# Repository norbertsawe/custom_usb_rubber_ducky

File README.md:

# Nodus — RP2040 Custom USB Keystroke Injection Platform

**Nodus** is a custom, ultra-compact USB Human Interface Device (HID) platform designed for keystroke injection, automated penetration testing, and security research. Powered by the Raspberry Pi RP2040 microcontroller, the board features dedicated high-speed QSPI flash memory, a precision external crystal oscillator for reliable USB PHY timing, and hardware physical controls for rapid reset and bootloader recovery.

---

## 📷 Board Hardware Overview

The PCB is custom designed in a standard USB stick form factor with an integrated PCB USB-A plug:

### Key Hardware Features

* **Microcontroller:** Raspberry Pi RP2040 Dual-Core ARM Cortex-M0+ running up to 133 MHz.
* **Storage:** High-speed QSPI NOR Flash IC for payload scripts and custom firmware storage.
* **Clock Source:** External 12 MHz Crystal Oscillator ensuring strict USB 2.0 full-speed timing stability.
* **On-Board Controls:**
  * **`B` (BOOTSEL):** Physical tactile button to force UF2 bootloader mode upon startup.
  * **`R` (RESET):** Hardware reset button for fast rebooting and rapid payload re-execution cycles without unplugging the drive.
* **Form Factor:** Slim, low-profile SMT design tailored for standard custom USB flash drive enclosures.

---

## 📊 Technical Specifications

| Component | Specification / Notes |
| :--- | :--- |
| **Core Processor** | RP2040 (Dual ARM Cortex-M0+, 264KB SRAM) |
| **Clock Source** | 12.000 MHz SMD Crystal Oscillator ($\pm$20 ppm) |
| **Flash Memory** | External QSPI NOR Flash (W25Qxx series or equivalent) |
| **Interface** | USB 2.0 Full-Speed (12 Mbps) Male USB-A Connector |
| **Power Supply** | 5V VBUS regulated via low-dropout (LDO) regulator to 3.3V |
| **Status Indicators** | Configurable User/Status LED(s) |
| **Debug & Control** | Tactical Boot/Reset switches, SWD target pads |

---

## 📁 Repository Structure

```

.
├── Hardware/            # KiCad schematics (.kicad_sch), PCB layouts (.kicad_pcb), and Gerber outputs
├── README.md            # Project overview and instructions
├── rubber_ducky_img1.png
├── rubber_ducky_img2.png
├── rubber_ducky_img3.png
└── rubber_ducky_img4.png

```

---

## 🚀 Quickstart & Hardware Testing

### 1. Putting the Board into Bootloader Mode
1. Plug the Nodus device into a host computer USB port.
2. Hold down the **`B` (BOOTSEL)** button and press the **`R` (RESET)** button once (or plug the device in while holding **`B`**).
3. Release the **`B`** button.
4. The device will enumerate as an external mass storage drive named `RPI-RP2`.

---

## 🛠 Firmware Development (WIP)

> [!NOTE]
> **Work In Progress:** Custom payload engines and dedicated firmware drivers are currently under active development. Hardware architecture and memory configurations are finalized.

Target build process once the C/C++ SDK engine is integrated:

```bash
cd Firmware
mkdir build && cd build
cmake ..
make -j$(nproc)

```

---

> [!WARNING]
> **Security & Usage Disclaimer**
> This hardware platform is intended exclusively for authorized security auditing, educational purposes, penetration testing, and legitimate research activities. Always obtain explicit written permission from system owners before testing or running payloads on any host environment.

---

## 📜 License

This project is licensed under the MIT License. See the `LICENSE` file for details.

```

```

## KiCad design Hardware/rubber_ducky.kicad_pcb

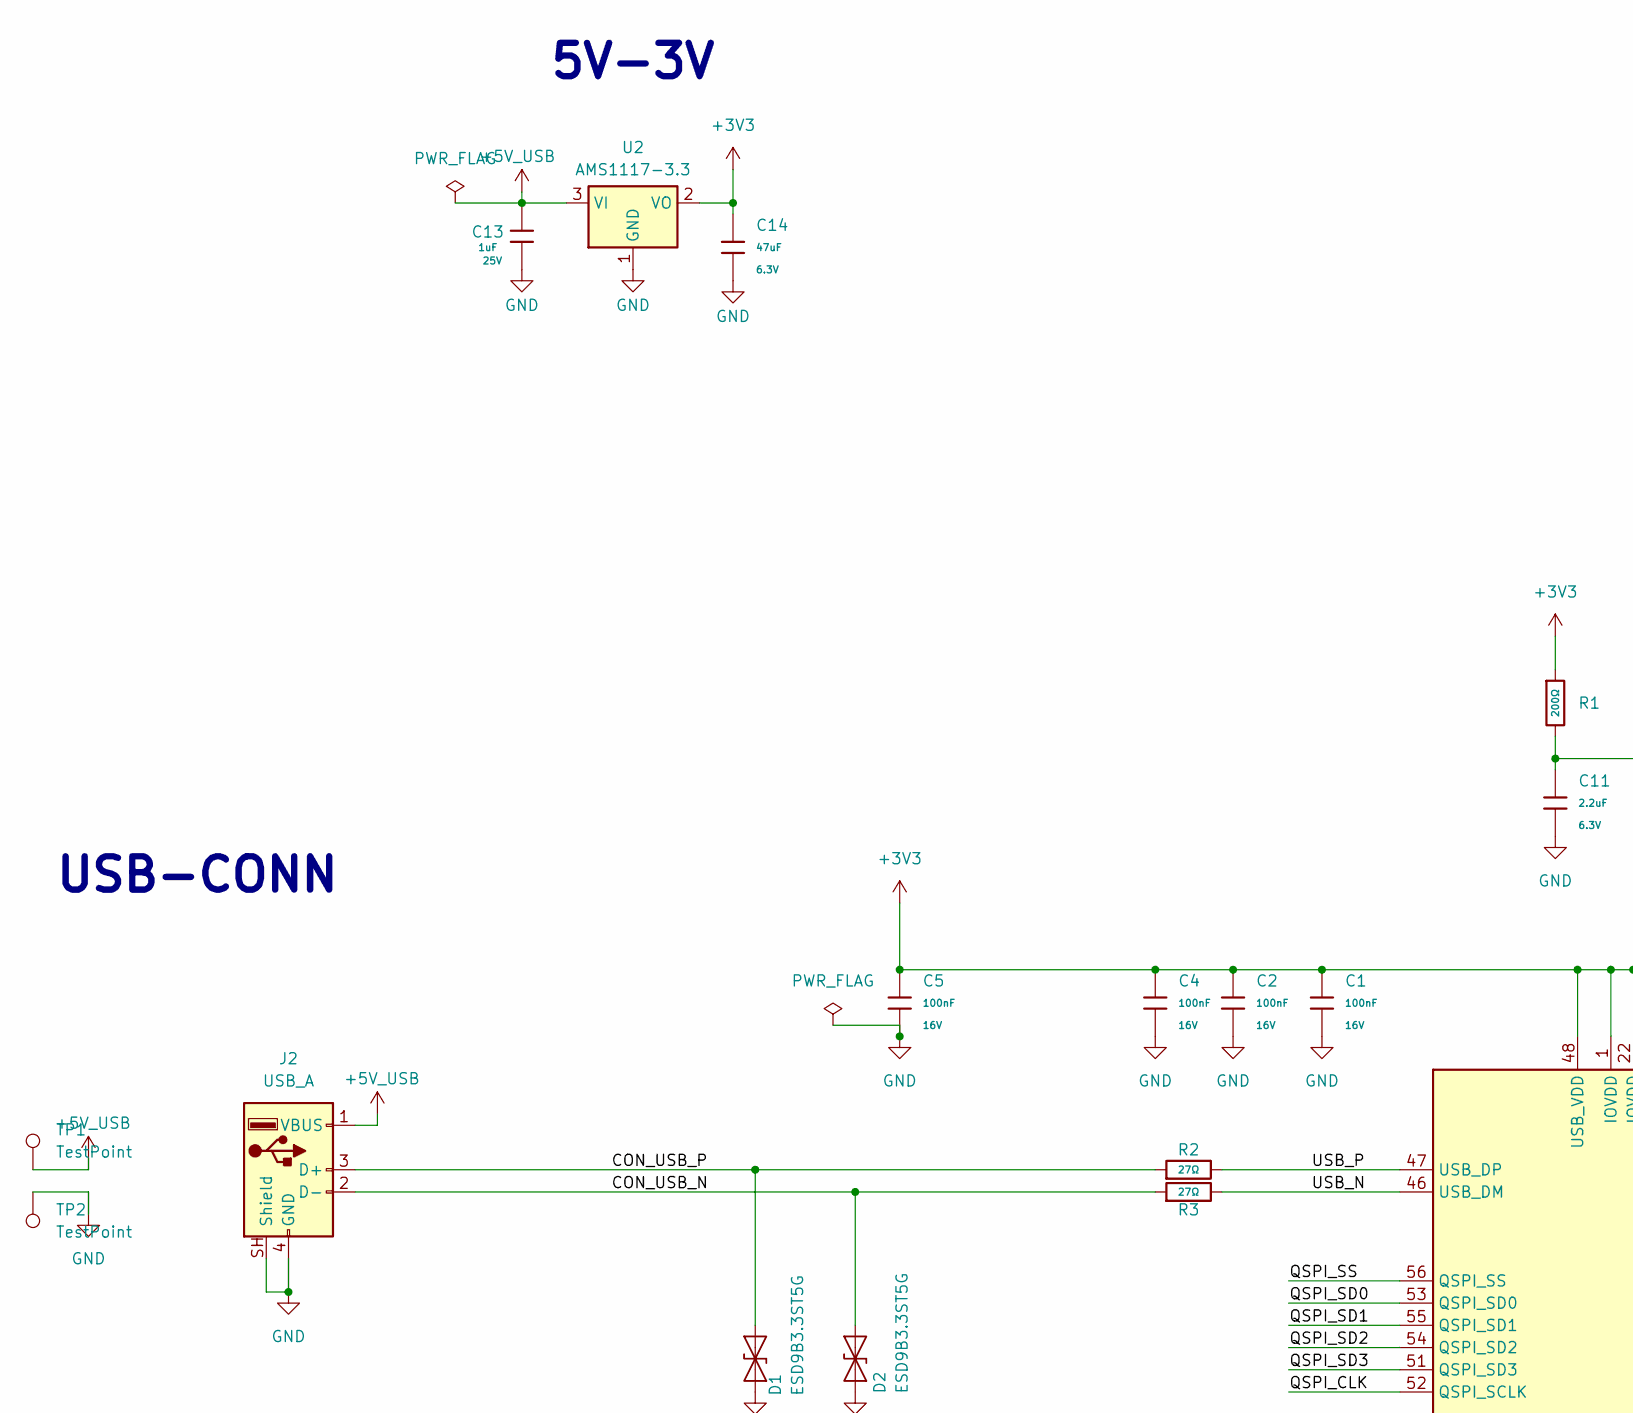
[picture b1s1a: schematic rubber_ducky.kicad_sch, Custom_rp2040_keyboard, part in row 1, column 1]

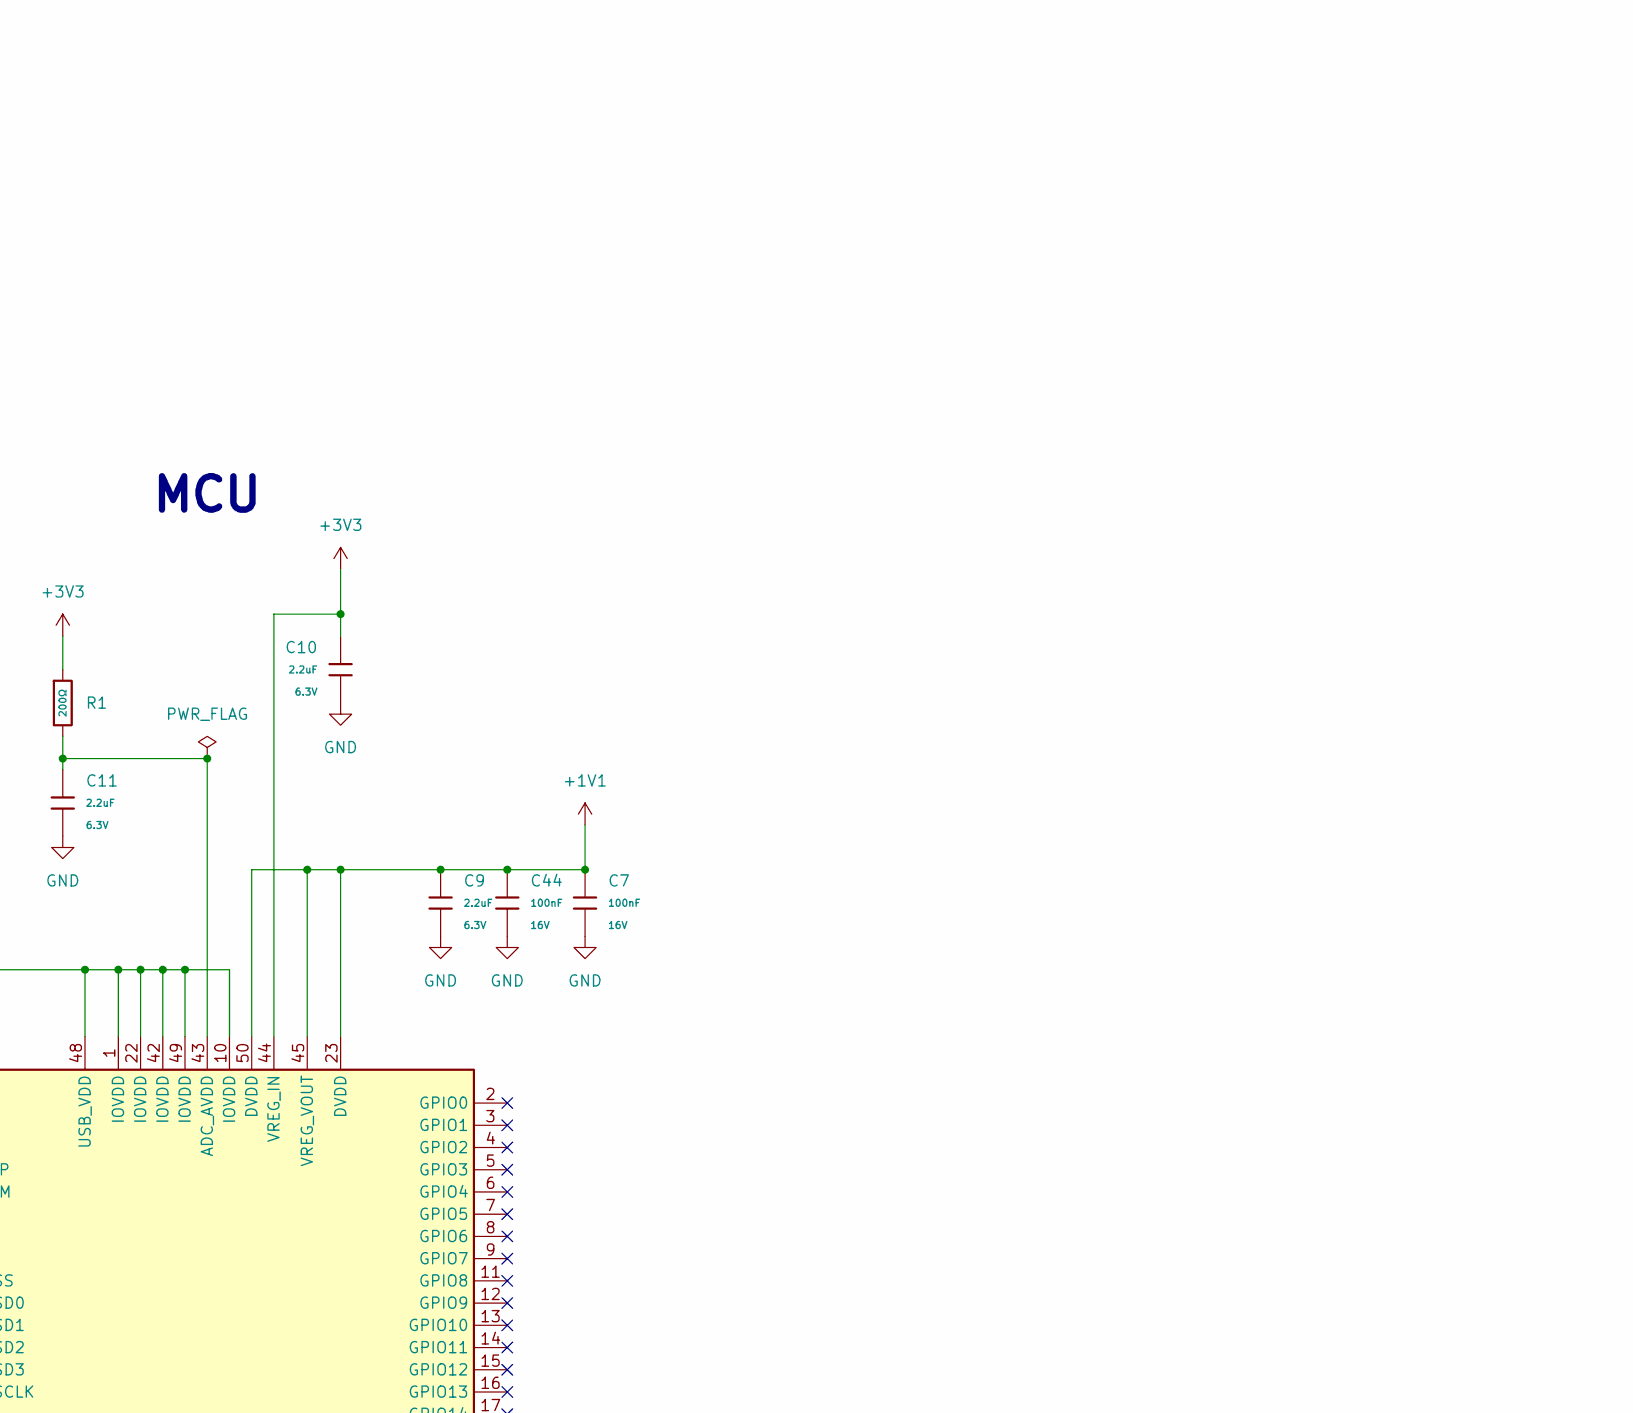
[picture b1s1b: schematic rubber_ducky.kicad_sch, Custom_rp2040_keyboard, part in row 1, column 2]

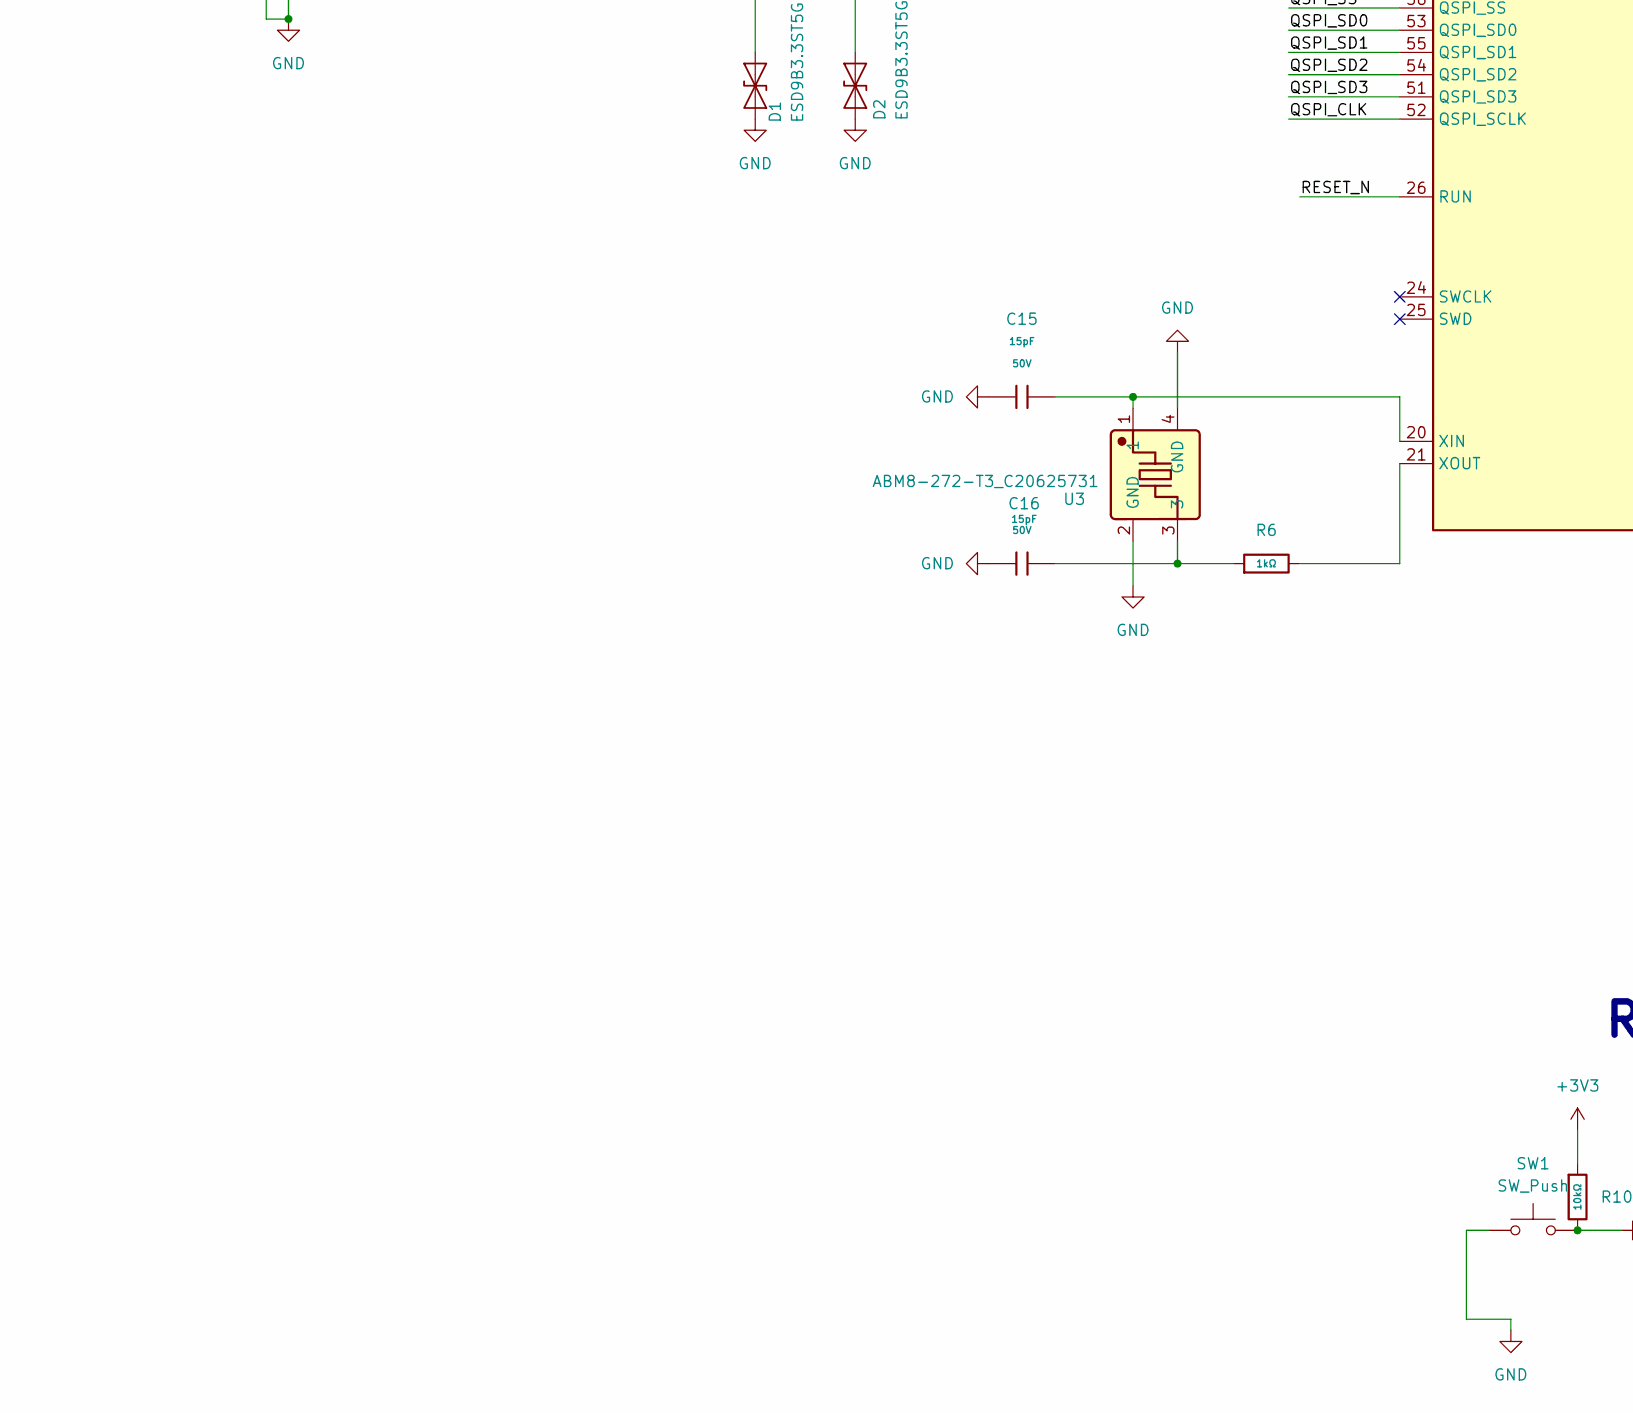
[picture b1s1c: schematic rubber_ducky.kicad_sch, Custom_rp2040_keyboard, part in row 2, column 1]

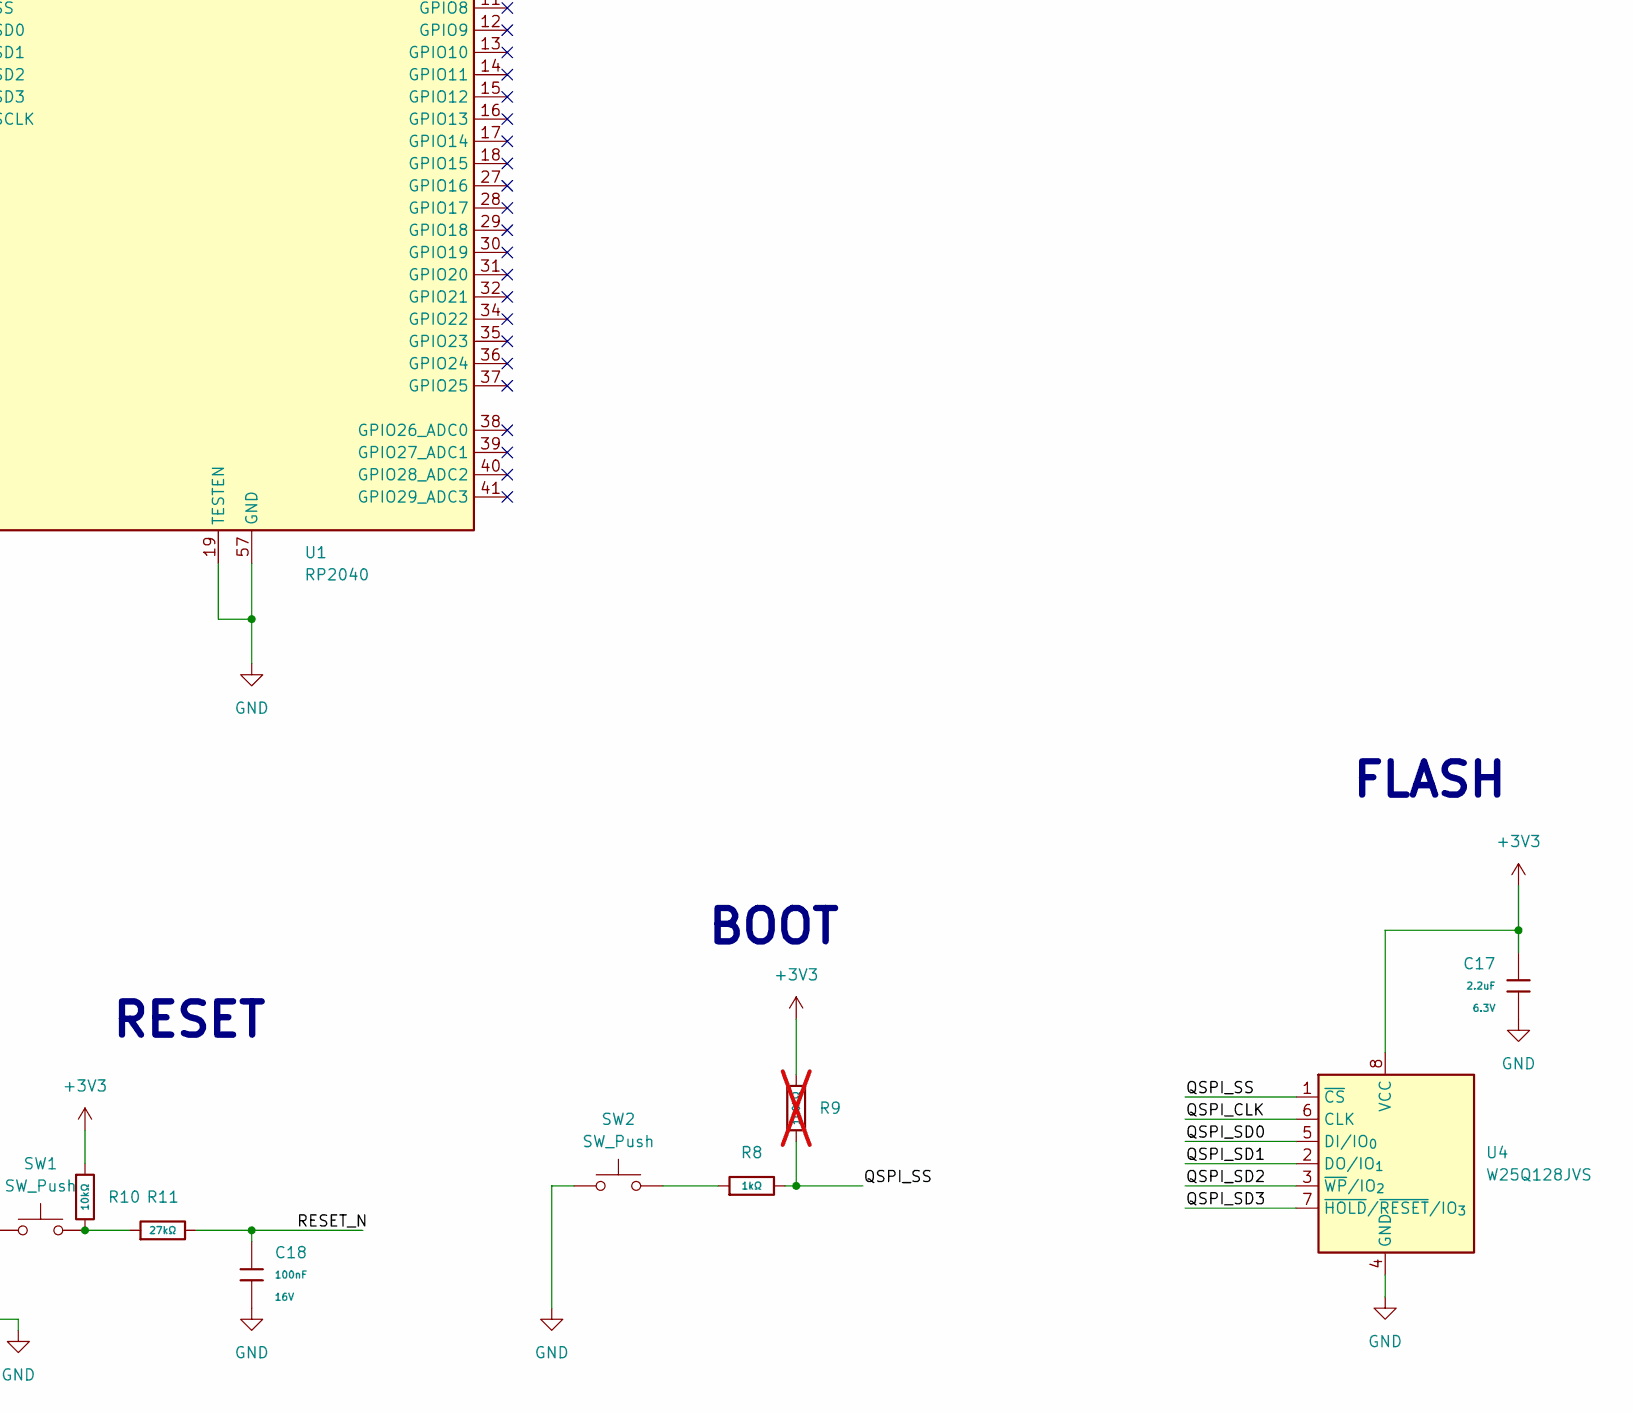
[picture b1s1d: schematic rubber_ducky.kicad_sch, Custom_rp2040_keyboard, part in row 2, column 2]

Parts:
C1, C2, C4, C5, C7, C18, C44: 100nF; C_0402; Voltage Rated 16V; Tolerance ±10%; Part CL05B104KO5NNNC; LCSC C1525
C9, C10, C11, C17: 2.2uF; C_0402; Voltage Rated 6.3V; Tolerance ±20%; Part CL05A225MQ5NSNC; LCSC C12530
C13: 1uF; C_0402; Voltage Rated 25V; Tolerance ±10%; Part CL05A105KA5NQNC; LCSC C52923
C14: 47uF; C_0805; Voltage Rated 6.3V; Tolerance ±20%; Part CL21A476MQYNNNE; LCSC C16780
C15, C16: 15pF; C_0402; Voltage Rated 50V; Tolerance ±5%; Part 0402CG150J500NT; LCSC C1548
D1, D2: ESD9B3.3ST5G; D_SOD-923
J2: USB_A; USB_A_CNCTech_1001-011-01101_Horizontal
R1: 200Ω; R_0402; Overload Voltage (Max) 50V; Tolerance ±1%; Part 0402WGF2000TCE; LCSC C25087
R2, R3: 27Ω; R_0402; Overload Voltage (Max) 50V; Tolerance ±1%; Part 0402WGF220JTCE; LCSC C25092
R6, R8: 1kΩ; R_0402; Overload Voltage (Max) 50V; Tolerance ±1%; Part 0402WGF1001TCE; LCSC C11702
R9: 100kΩ; R_0402; Overload Voltage (Max) 50V; Tolerance ±1%; Part 0402WGF1003TCE; LCSC C25741; not fitted
R10: 10kΩ; R_0402; Overload Voltage (Max) 50V; Tolerance ±1%; Part 0402WGF1002TCE; LCSC C25744
R11: 27kΩ; R_0402; Overload Voltage (Max) 50V; Tolerance ±1%; Part 0402WGF2702TCE; LCSC C25771
SW1, SW2: SW_Push; SW_SPST_B3U-1000P-B
TP1, TP2: TestPoint; TestPoint_Pad_1.5x1.5mm
U1: RP2040; QFN-56-1EP_7x7mm_P0.4mm_EP3.2x3.2mm_ThermalVias; LCSC C2040
U2: AMS1117-3.3; SOT-223-3_TabPin2
U3: ABM8-272-T3_C20625731; OSC-SMD_4P-L3.2-W2.5-BL; Manufacturer Part ABM8-272-T3; LCSC C20625731
U4: W25Q128JVS; SOIC-8_5.3x5.3mm_P1.27mm

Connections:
+1V1: C7.2, C9.1, C44.2, U1.23 (DVDD), U1.45 (VREG_VOUT), U1.50 (DVDD)
+3V3: C1.2, C2.2, C4.2, C5.2, C10.1, C14.1, C17.1, R1.1, R9.1, R10.1, U1.1 (IOVDD), U1.10 (IOVDD), U1.22 (IOVDD), U1.42 (IOVDD), U1.44 (VREG_IN), U1.48 (USB_VDD), U1.49 (IOVDD), U2.2 (VO), U4.8 (VCC); also elsewhere on the board
+5V_USB: C13.1, J2.1 (VBUS), TP1.1 (1_1), U2.3 (VI)
/CON_USB_N: D2.2 (A2), J2.2 (D-), R3.1
/CON_USB_P: D1.2 (A2), J2.3 (D+), R2.1
/QSPI_CLK: U1.52 (QSPI_SCLK), U4.6 (CLK)
/QSPI_SD0: U1.53 (QSPI_SD0), U4.5 (DI/IO_{0})
/QSPI_SD1: U1.55 (QSPI_SD1), U4.2 (DO/IO_{1})
/QSPI_SD2: U1.54 (QSPI_SD2), U4.3 (~WP/IO_{2})
/QSPI_SD3: U1.51 (QSPI_SD3), U4.7 (~HOLD/~RESET/IO_{3})
/QSPI_SS: R8.2, R9.2, U1.56 (QSPI_SS), U4.1 (~CS)
/RESET_N: C18.2, R11.2, U1.26 (RUN)
/USB_N: R3.2, U1.46 (USB_DM)
/USB_P: R2.2, U1.47 (USB_DP)
GND: C1.1, C2.1, C4.1, C5.1, C7.1, C9.2, C10.2, C11.2, C13.2, C14.2, C15.1, C16.1, C17.2, C18.1, C44.1, D1.1 (A1), D2.1 (A1), J2.4 (GND), J2.SH (Shield), SW1.1, SW2.1, TP2.1 (1_1), U1.19 (TESTEN), U1.57 (GND), U2.1 (GND), U3.2 (GND), U3.4 (GND), U4.4 (GND); also elsewhere on the board
unnamed: C16.2, R6.1, U3.3
unnamed: R8.1, SW2.2
unnamed: R10.2, R11.1, SW1.2
unnamed: C11.1, R1.2, U1.43 (ADC_AVDD)
unnamed: C15.2, U1.20 (XIN), U3.1
unnamed: R6.2, U1.21 (XOUT)

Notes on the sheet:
MCU
BOOT
FLASH
USB-CONN
RESET
5V-3V

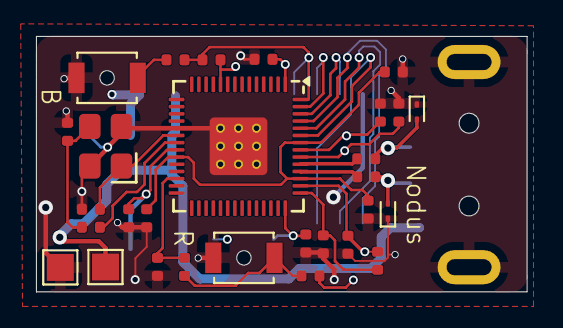
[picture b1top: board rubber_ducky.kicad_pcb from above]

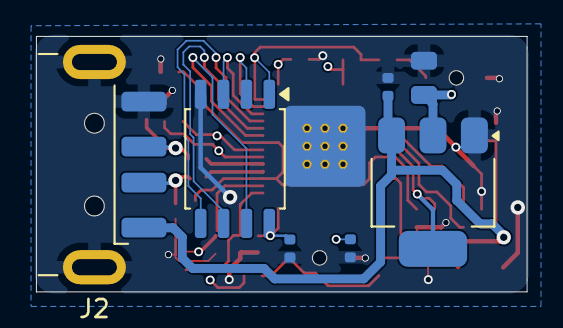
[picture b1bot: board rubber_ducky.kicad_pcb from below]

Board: 4 copper layers, 27.3 x 14.2 mm, 36 parts (7 on the bottom side), 21 nets.

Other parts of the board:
C3, C6: 100nF; C_0402

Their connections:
+3V3: C3.2, C6.2; also elsewhere on the board
GND: C3.1, C6.1; also elsewhere on the board

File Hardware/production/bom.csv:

Designator,Footprint,Quantity,Value,LCSC Part #
"C1, C18, C2, C3, C4, C44, C5, C6, C7",C_0402,9,100nF,C1525
"C10, C11, C17, C9",C_0402,4,2.2uF,C12530
C13,C_0402,1,1uF,C52923
C14,C_0805,1,47uF,C16780
"C15, C16",C_0402,2,15pF,C1548
"D1, D2",D_SOD-923,2,ESD9B3.3ST5G,
J2,USB_A_CNCTech_1001-011-01101_Horizontal,1,USB_A,
R1,R_0402,1,200Ω,C25087
R10,R_0402,1,10kΩ,C25744
R11,R_0402,1,27kΩ,C25771
"R2, R3",R_0402,2,27Ω,C25092
"R6, R8",R_0402,2,1kΩ,C11702
"SW1, SW2",SW_SPST_B3U-1000P-B,2,SW_Push,
"TP1, TP2",TestPoint_Pad_1.5x1.5mm,2,TestPoint,
U1,QFN-56-1EP_7x7mm_P0.4mm_EP3.2x3.2mm_ThermalVias,1,RP2040,C2040
U2,SOT-223-3_TabPin2,1,AMS1117-3.3,
U3,OSC-SMD_4P-L3.2-W2.5-BL,1,ABM8-272-T3_C20625731,C20625731
U4,SOIC-8_5.3x5.3mm_P1.27mm,1,W25Q128JVS,

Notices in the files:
README.md:
License: MIT
